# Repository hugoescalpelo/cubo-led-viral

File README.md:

# cubo-led-viral
En este repositorio se encuentra el codigo correspondiente al cubo led en colaboración con Anni Garza Lau, Liliana Dominguez y Yunuen Lenin

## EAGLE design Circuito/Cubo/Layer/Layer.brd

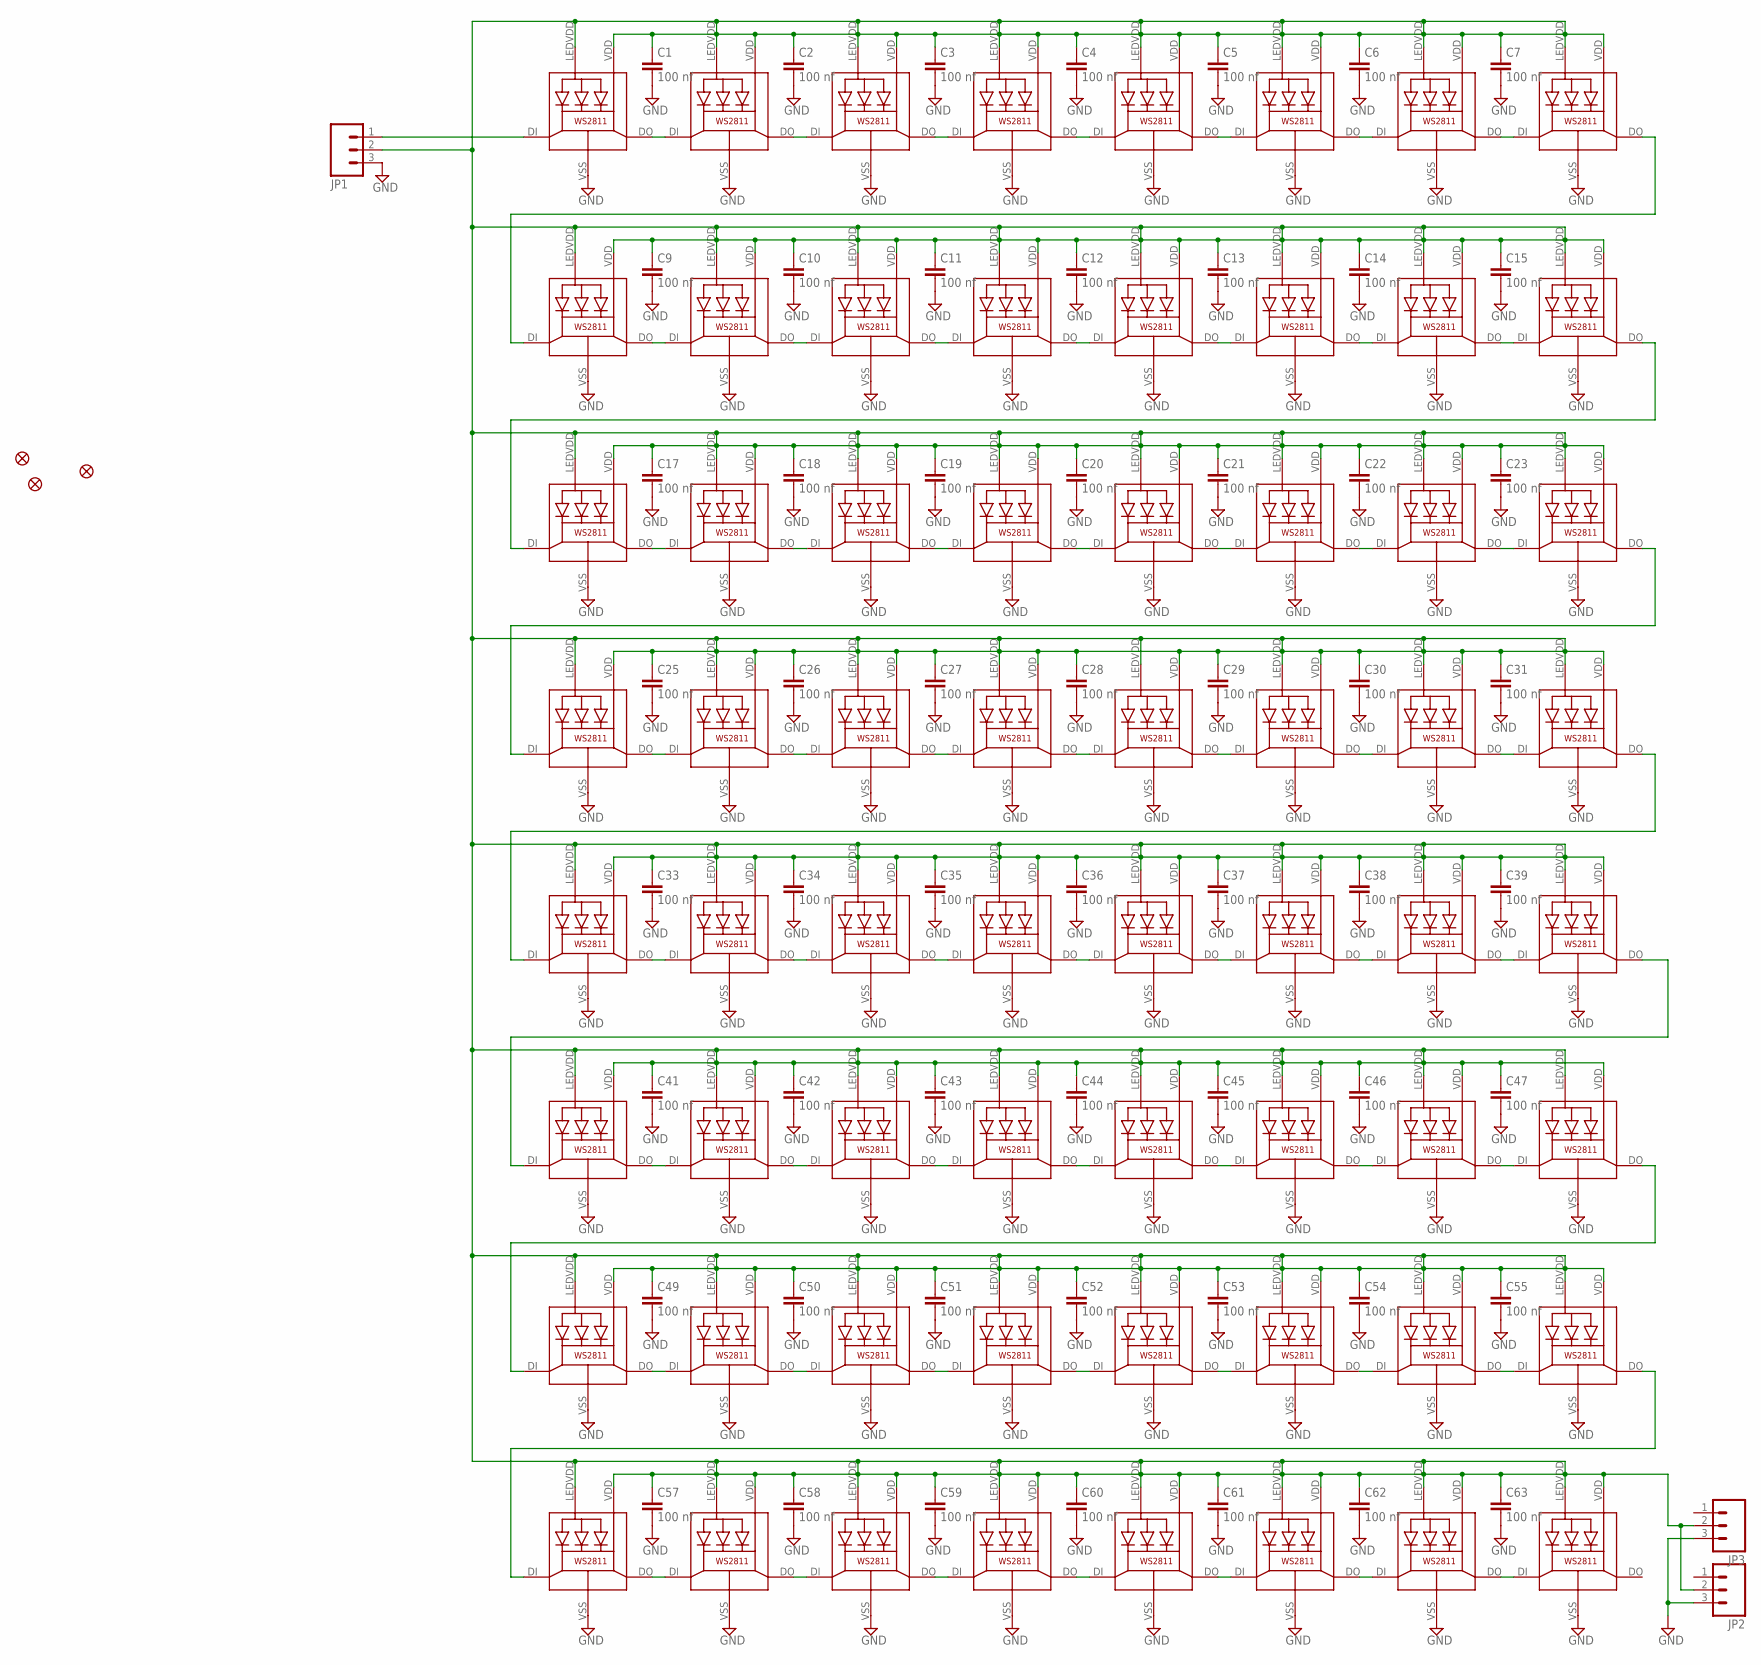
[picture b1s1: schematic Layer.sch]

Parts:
C1, C2, C3, C4, C5, C6, C7, C9, C10, C11, C12, C13, C14, C15, C17, C18, C19, C20, C21, C22, C23, C25, C26, C27, C28, C29, C30, C31, C33, C34, C35, C36, C37, C38, C39, C41, C42, C43, C44, C45, C46, C47, C49, C50, C51, C52, C53, C54, C55, C57, C58, C59, C60, C61, C62, C63: 100 nf; C0805
FID1, FID2, FID3: FIDUCIAL""; FIDUCIAL_1MM
JP1, JP2, JP3: M03PTH; 1X03
LED1, LED2, LED3, LED4, LED5, LED6, LED7, LED8, LED9, LED10, LED11, LED12, LED13, LED14, LED15, LED16, LED17, LED18, LED19, LED20, LED21, LED22, LED23, LED24, LED25, LED26, LED27, LED28, LED29, LED30, LED31, LED32, LED33, LED34, LED35, LED36, LED37, LED38, LED39, LED40, LED41, LED42, LED43, LED44, LED45, LED46, LED47, LED48, LED49, LED50, LED51, LED52, LED53, LED54, LED55, LED56, LED57, LED58, LED59, LED60, LED61, LED62, LED63, LED64: WS28115050

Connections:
GND: C1.2, C2.2, C3.2, C4.2, C5.2, C6.2, C7.2, C9.2, C10.2, C11.2, C12.2, C13.2, C14.2, C15.2, C17.2, C18.2, C19.2, C20.2, C21.2, C22.2, C23.2, C25.2, C26.2, C27.2, C28.2, C29.2, C30.2, C31.2, C33.2, C34.2, C35.2, C36.2, C37.2, C38.2, C39.2, C41.2, C42.2, C43.2, C44.2, C45.2, C46.2, C47.2, C49.2, C50.2, C51.2, C52.2, C53.2, C54.2, C55.2, C57.2, C58.2, C59.2, C60.2, C61.2, C62.2, C63.2, JP1.3, JP2.3, JP3.3, LED1.VSS (GND), LED2.VSS (GND), LED3.VSS (GND), LED4.VSS (GND), LED5.VSS (GND), LED6.VSS (GND), LED7.VSS (GND), LED8.VSS (GND), LED9.VSS (GND), LED10.VSS (GND), LED11.VSS (GND), LED12.VSS (GND), LED13.VSS (GND), LED14.VSS (GND), LED15.VSS (GND), LED16.VSS (GND), LED17.VSS (GND), LED18.VSS (GND), LED19.VSS (GND), LED20.VSS (GND), LED21.VSS (GND), LED22.VSS (GND), LED23.VSS (GND), LED24.VSS (GND), LED25.VSS (GND), LED26.VSS (GND), LED27.VSS (GND), LED28.VSS (GND), LED29.VSS (GND), LED30.VSS (GND), LED31.VSS (GND), LED32.VSS (GND), LED33.VSS (GND), LED34.VSS (GND), LED35.VSS (GND), LED36.VSS (GND), LED37.VSS (GND), LED38.VSS (GND), LED39.VSS (GND), LED40.VSS (GND), LED41.VSS (GND), LED42.VSS (GND), LED43.VSS (GND), LED44.VSS (GND), LED45.VSS (GND), LED46.VSS (GND), LED47.VSS (GND), LED48.VSS (GND), LED49.VSS (GND), LED50.VSS (GND), LED51.VSS (GND), LED52.VSS (GND), LED53.VSS (GND), LED54.VSS (GND), LED55.VSS (GND), LED56.VSS (GND), LED57.VSS (GND), LED58.VSS (GND), LED59.VSS (GND), LED60.VSS (GND), LED61.VSS (GND), LED62.VSS (GND), LED63.VSS (GND), LED64.VSS (GND)
unnamed: JP1.1, LED1.DI
unnamed: LED8.DO, LED9.DI
unnamed: LED16.DO, LED17.DI
unnamed: LED24.DO, LED25.DI
unnamed: LED40.DO, LED41.DI
unnamed: LED32.DO, LED33.DI
unnamed: LED48.DO, LED49.DI
unnamed: LED56.DO, LED57.DI
unnamed: LED17.DO, LED18.DI
unnamed: LED25.DO, LED26.DI
unnamed: LED26.DO, LED27.DI
unnamed: LED2.DO, LED3.DI
unnamed: LED3.DO, LED4.DI
unnamed: LED4.DO, LED5.DI
unnamed: LED5.DO, LED6.DI
unnamed: LED6.DO, LED7.DI
unnamed: LED7.DO, LED8.DI
unnamed: LED10.DO, LED11.DI
unnamed: LED11.DO, LED12.DI
unnamed: LED12.DO, LED13.DI
unnamed: LED13.DO, LED14.DI
unnamed: LED14.DO, LED15.DI
unnamed: LED15.DO, LED16.DI
unnamed: LED18.DO, LED19.DI
unnamed: LED19.DO, LED20.DI
unnamed: LED20.DO, LED21.DI
unnamed: LED21.DO, LED22.DI
unnamed: LED22.DO, LED23.DI
unnamed: LED23.DO, LED24.DI
unnamed: LED27.DO, LED28.DI
unnamed: LED28.DO, LED29.DI
unnamed: LED29.DO, LED30.DI
unnamed: LED30.DO, LED31.DI
unnamed: LED31.DO, LED32.DI
unnamed: LED1.DO, LED2.DI
unnamed: LED9.DO, LED10.DI
unnamed: LED49.DO, LED50.DI
unnamed: LED57.DO, LED58.DI
unnamed: LED58.DO, LED59.DI
unnamed: LED34.DO, LED35.DI
unnamed: LED35.DO, LED36.DI
unnamed: LED36.DO, LED37.DI
unnamed: LED37.DO, LED38.DI
unnamed: LED38.DO, LED39.DI
unnamed: LED39.DO, LED40.DI
unnamed: LED42.DO, LED43.DI
unnamed: LED43.DO, LED44.DI
unnamed: LED44.DO, LED45.DI
unnamed: LED45.DO, LED46.DI
unnamed: LED46.DO, LED47.DI
unnamed: LED47.DO, LED48.DI
unnamed: LED50.DO, LED51.DI
unnamed: LED51.DO, LED52.DI
unnamed: LED52.DO, LED53.DI
unnamed: LED53.DO, LED54.DI
unnamed: LED54.DO, LED55.DI
unnamed: LED55.DO, LED56.DI
unnamed: LED59.DO, LED60.DI
unnamed: LED60.DO, LED61.DI
unnamed: LED61.DO, LED62.DI
unnamed: LED62.DO, LED63.DI
unnamed: LED63.DO, LED64.DI
unnamed: LED33.DO, LED34.DI
unnamed: LED41.DO, LED42.DI
VDD: C1.1, C2.1, C3.1, C4.1, C5.1, C6.1, C7.1, C9.1, C10.1, C11.1, C12.1, C13.1, C14.1, C15.1, C17.1, C18.1, C19.1, C20.1, C21.1, C22.1, C23.1, C25.1, C26.1, C27.1, C28.1, C29.1, C30.1, C31.1, C33.1, C34.1, C35.1, C36.1, C37.1, C38.1, C39.1, C41.1, C42.1, C43.1, C44.1, C45.1, C46.1, C47.1, C49.1, C50.1, C51.1, C52.1, C53.1, C54.1, C55.1, C57.1, C58.1, C59.1, C60.1, C61.1, C62.1, C63.1, JP1.2, JP2.2, JP3.2, LED1.LEDVDD, LED1.VDD, LED2.LEDVDD, LED2.VDD, LED3.LEDVDD, LED3.VDD, LED4.LEDVDD, LED4.VDD, LED5.LEDVDD, LED5.VDD, LED6.LEDVDD, LED6.VDD, LED7.LEDVDD, LED7.VDD, LED8.LEDVDD, LED8.VDD, LED9.LEDVDD, LED9.VDD, LED10.LEDVDD, LED10.VDD, LED11.LEDVDD, LED11.VDD, LED12.LEDVDD, LED12.VDD, LED13.LEDVDD, LED13.VDD, LED14.LEDVDD, LED14.VDD, LED15.LEDVDD, LED15.VDD, LED16.LEDVDD, LED16.VDD, LED17.LEDVDD, LED17.VDD, LED18.LEDVDD, LED18.VDD, LED19.LEDVDD, LED19.VDD, LED20.LEDVDD, LED20.VDD, LED21.LEDVDD, LED21.VDD, LED22.LEDVDD, LED22.VDD, LED23.LEDVDD, LED23.VDD, LED24.LEDVDD, LED24.VDD, LED25.LEDVDD, LED25.VDD, LED26.LEDVDD, LED26.VDD, LED27.LEDVDD, LED27.VDD, LED28.LEDVDD, LED28.VDD, LED29.LEDVDD, LED29.VDD, LED30.LEDVDD, LED30.VDD, LED31.LEDVDD, LED31.VDD, LED32.LEDVDD, LED32.VDD, LED33.LEDVDD, LED33.VDD, LED34.LEDVDD, LED34.VDD, LED35.LEDVDD, LED35.VDD, LED36.LEDVDD, LED36.VDD, LED37.LEDVDD, LED37.VDD, LED38.LEDVDD, LED38.VDD, LED39.LEDVDD, LED39.VDD, LED40.LEDVDD, LED40.VDD, LED41.LEDVDD, LED41.VDD, LED42.LEDVDD, LED42.VDD, LED43.LEDVDD, LED43.VDD, LED44.LEDVDD, LED44.VDD, LED45.LEDVDD, LED45.VDD, LED46.LEDVDD, LED46.VDD, LED47.LEDVDD, LED47.VDD, LED48.LEDVDD, LED48.VDD, LED49.LEDVDD, LED49.VDD, LED50.LEDVDD, LED50.VDD, LED51.LEDVDD, LED51.VDD, LED52.LEDVDD, LED52.VDD, LED53.LEDVDD, LED53.VDD, LED54.LEDVDD, LED54.VDD, LED55.LEDVDD, LED55.VDD, LED56.LEDVDD, LED56.VDD, LED57.LEDVDD, LED57.VDD, LED58.LEDVDD, LED58.VDD, LED59.LEDVDD, LED59.VDD, LED60.LEDVDD, LED60.VDD, LED61.LEDVDD, LED61.VDD, LED62.LEDVDD, LED62.VDD, LED63.LEDVDD, LED63.VDD, LED64.LEDVDD, LED64.VDD

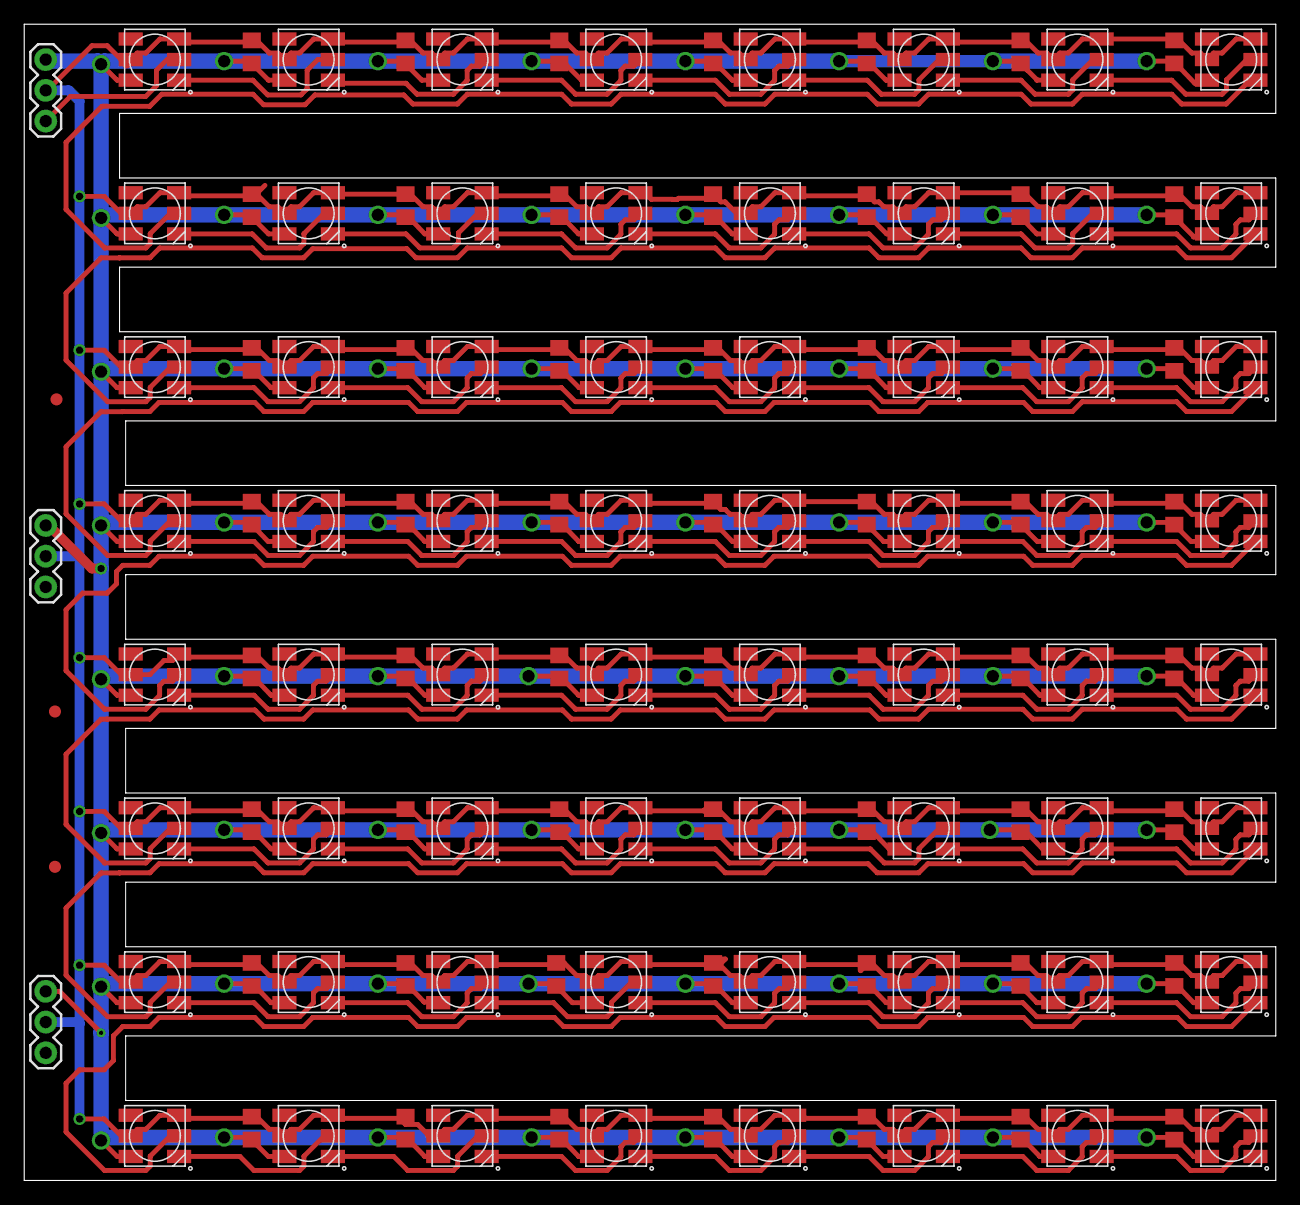
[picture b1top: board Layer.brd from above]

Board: 2 copper layers, 103.4 x 95.5 mm, 126 parts (0 on the bottom side), 66 nets.

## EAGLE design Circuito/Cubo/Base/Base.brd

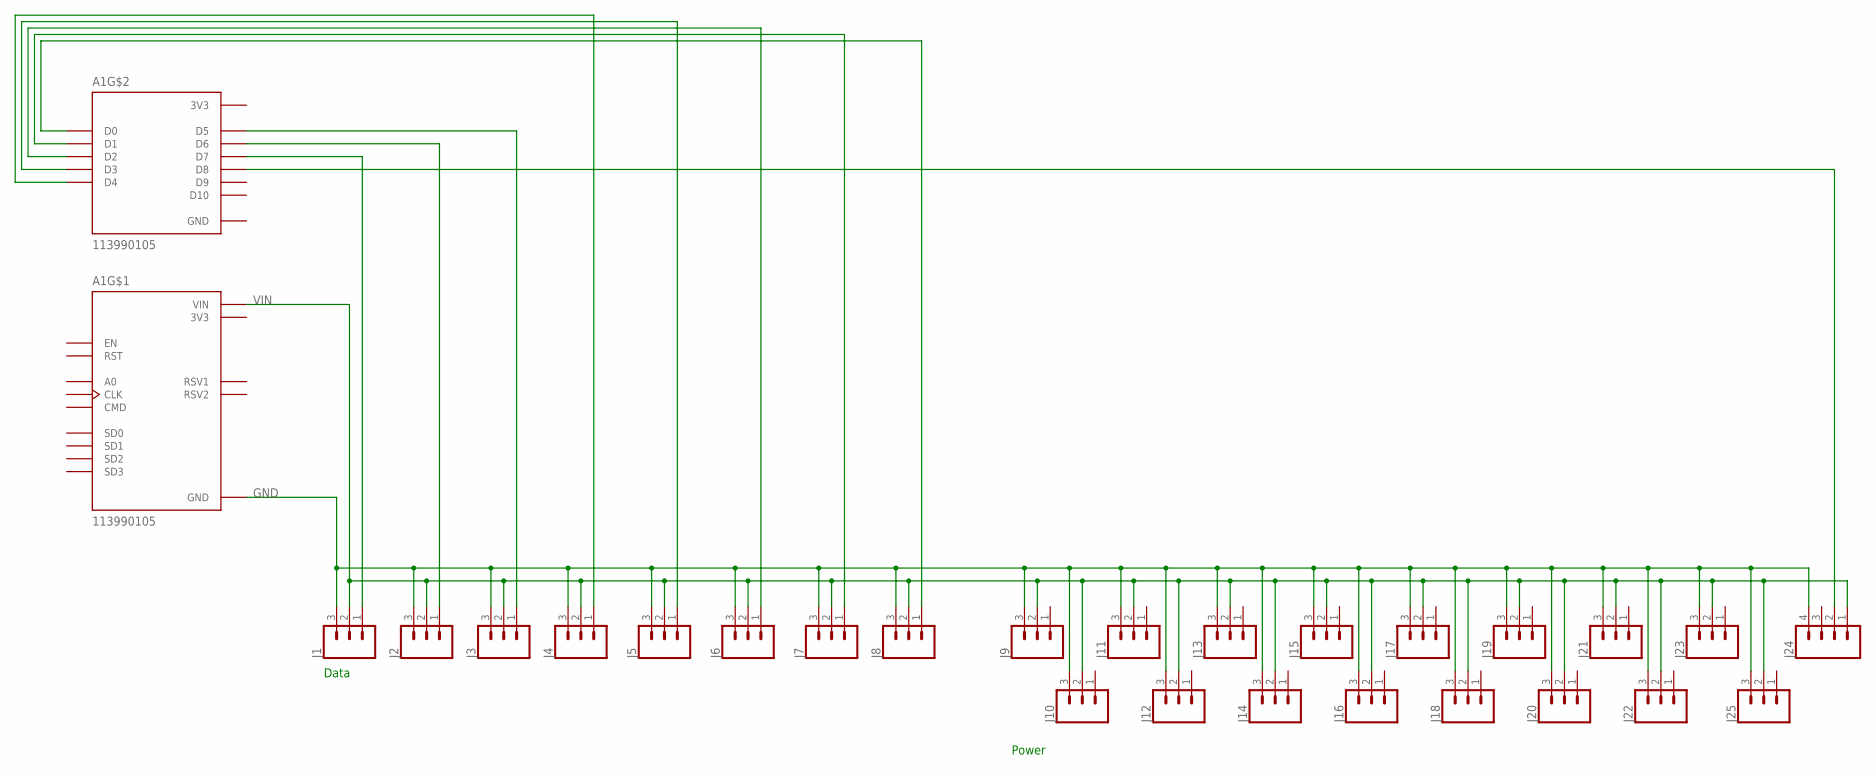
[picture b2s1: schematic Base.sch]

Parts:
A1: 113990105; SEEED_113990105
J1, J2, J3, J4, J5, J6, J7, J8, J9, J10, J11, J12, J13, J14, J15, J16, J17, J18, J19, J20, J21, J22, J23, J25: CONN_03; 1X03
J24: CONN_04; 1X04

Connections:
3V3: A1.J1_11 (3V3), A1.J2_6 (3V3), A1.J2_15 (3V3)
GND: A1.J1_10 (GND), A1.J1_14 (GND), A1.J2_7 (GND), A1.J2_14 (GND), J1.3, J2.3, J3.3, J4.3, J5.3, J6.3, J7.3, J8.3, J9.3, J10.3, J11.3, J12.3, J13.3, J14.3, J15.3, J16.3, J17.3, J18.3, J19.3, J20.3, J21.3, J22.3, J23.3, J24.4, J25.3
unnamed: A1.J2_10 (D7), J1.1
unnamed: A1.J2_9 (D6), J2.1
unnamed: A1.J2_8 (D5), J3.1
unnamed: A1.J2_5 (D4), J4.1
unnamed: A1.J2_4 (D3), J5.1
unnamed: A1.J2_3 (D2), J6.1
unnamed: A1.J2_2 (D1), J7.1
unnamed: A1.J2_1 (D0), J8.1
unnamed: A1.J2_11 (D8), J24.2
VIN: A1.J1_15 (VIN), J1.2, J2.2, J3.2, J4.2, J5.2, J6.2, J7.2, J8.2, J9.2, J10.2, J11.2, J12.2, J13.2, J14.2, J15.2, J16.2, J17.2, J18.2, J19.2, J20.2, J21.2, J22.2, J23.2, J24.1, J25.2

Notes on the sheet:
Data
Power

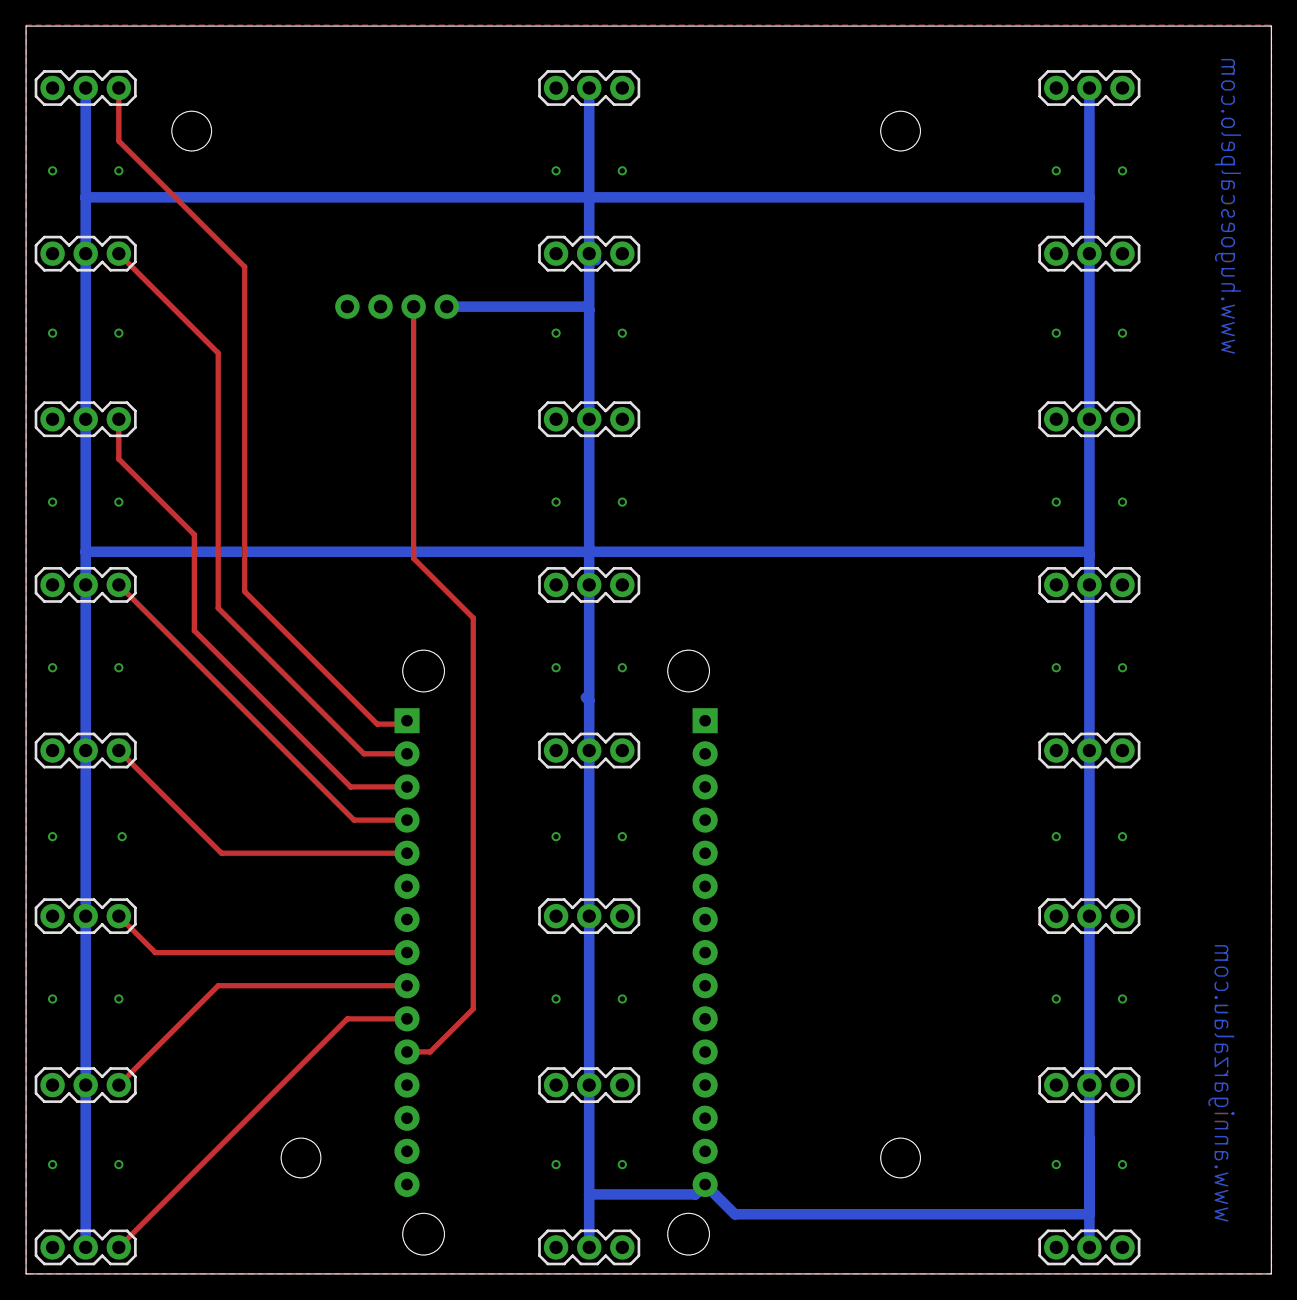
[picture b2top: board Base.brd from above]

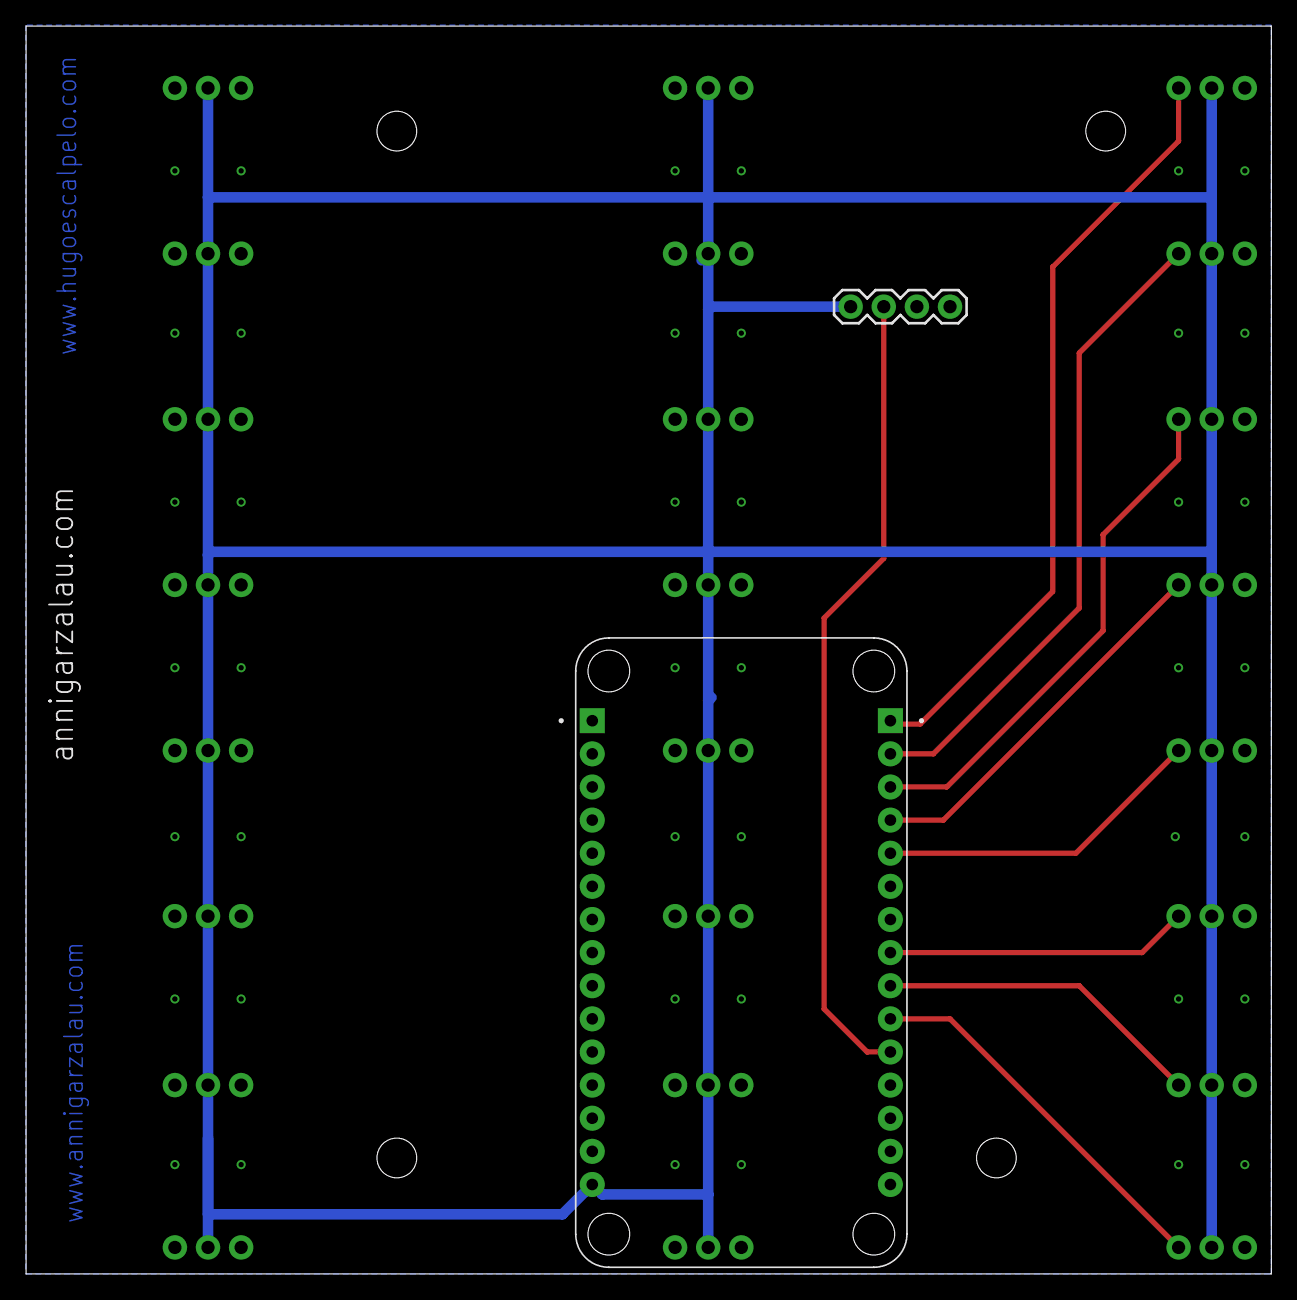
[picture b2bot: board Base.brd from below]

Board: 2 copper layers, 95.5 x 95.7 mm, 26 parts (2 on the bottom side), 12 nets.

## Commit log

2021-12-02 Codigo cargado
2022-03-14 new notes
2022-03-15 Cambios simples a las notas
2022-08-10 actualización

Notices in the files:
parts and their libraries:
SparkFun-Connectors: Licensing: Creative Commons ShareAlike 4.0 International - https://creativecommons.org/licenses/by-sa/4.0
microbuilder: This work is placed in the public domain, and may be freely used for commercial and non-commercial work with the following conditions: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
